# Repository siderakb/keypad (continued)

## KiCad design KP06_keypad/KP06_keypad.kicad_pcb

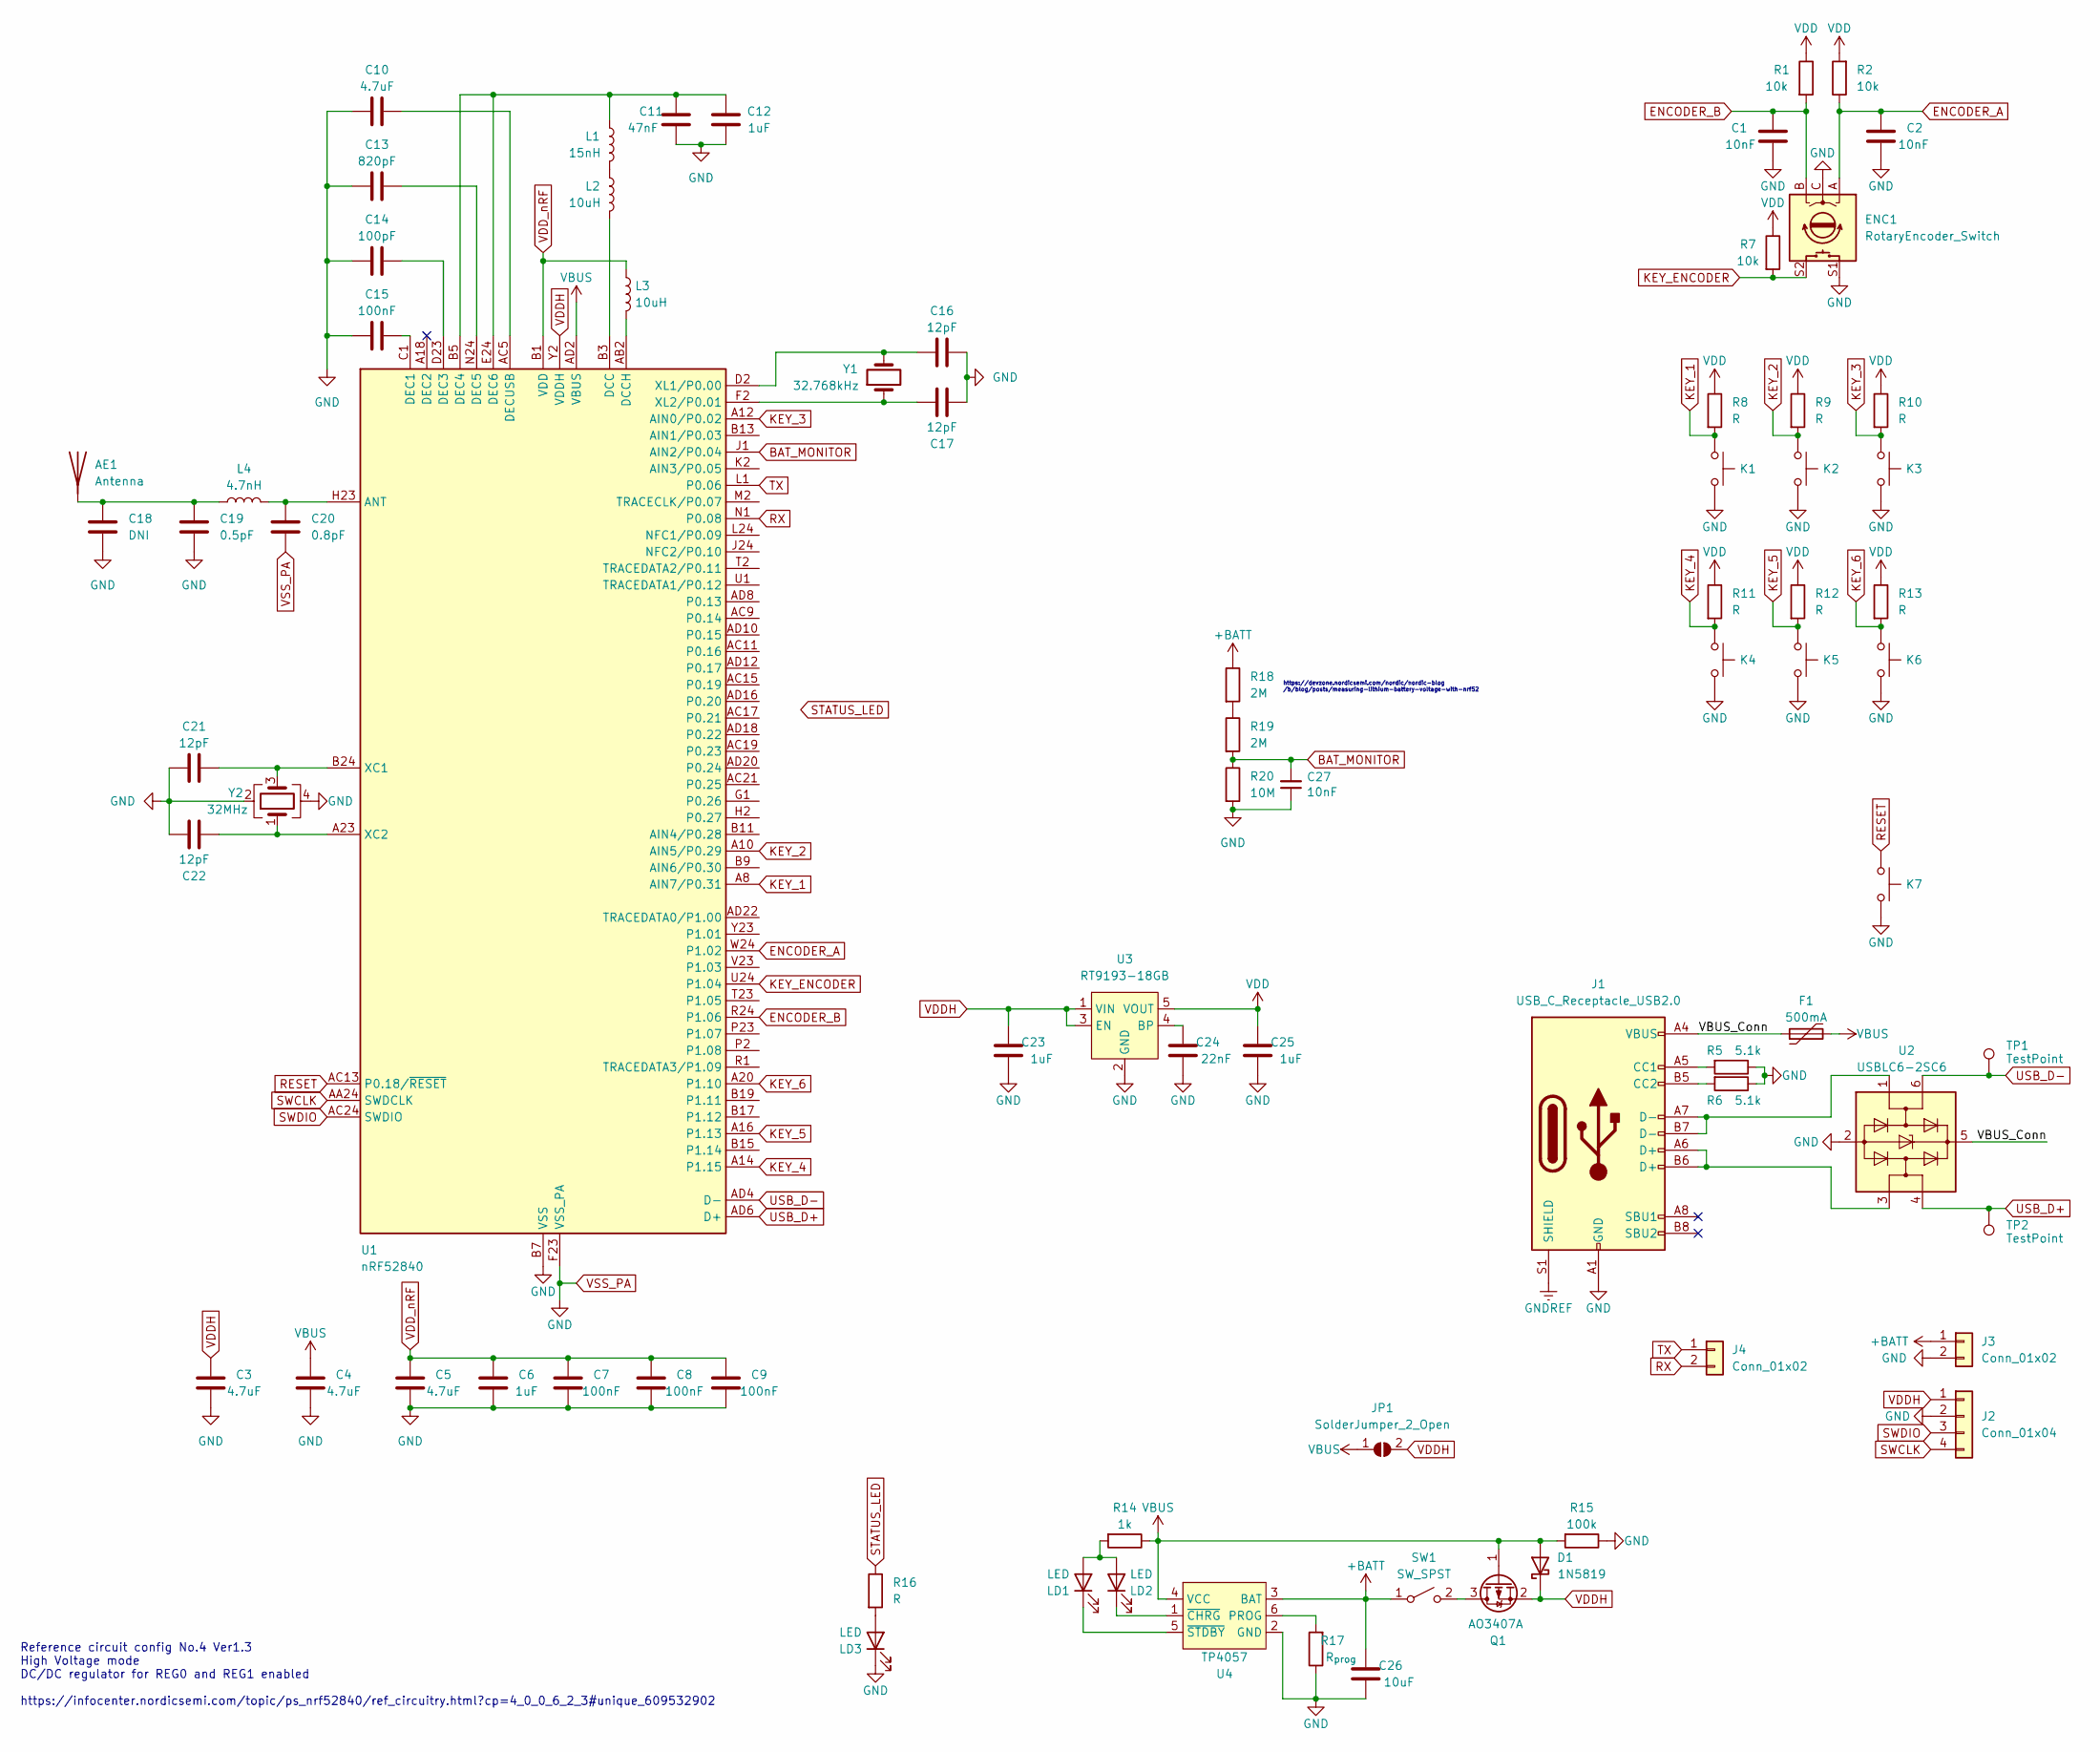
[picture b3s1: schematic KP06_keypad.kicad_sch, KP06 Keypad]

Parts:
AE1: Antenna; Texas_SWRA117D_2.4GHz_Left
C1, C2, C27: 10nF; C_0603_1608Metric
C3, C4, C5, C10: 4.7uF; C_0603_1608Metric
C6, C12, C23, C25: 1uF; C_0603_1608Metric
C7, C8, C9, C15: 100nF; C_0402_1005Metric
C11: 47nF; C_0402_1005Metric
C13: 820pF; C_0402_1005Metric
C14: 100pF; C_0402_1005Metric
C16, C17, C21, C22: 12pF; C_0402_1005Metric
C18: DNI; C_0402_1005Metric
C19: 0.5pF; C_0402_1005Metric
C20: 0.8pF; C_0402_1005Metric
C24: 22nF; C_0603_1608Metric
C26: 10uF; C_0603_1608Metric
D1: 1N5819; D_SOD-123
ENC1: RotaryEncoder_Switch; RotaryEncoder_Alps_EC11E-Switch_Vertical_H20mm
F1: 500mA; Fuse_1206_3216Metric
J1: USB_C_Receptacle_USB2.0; USB_C_Receptacle_HRO_TYPE-C-31-M-12
J2: Conn_01x04; PinHeader_1x04_P2.54mm_Vertical
J3: Conn_01x02; JST_PH_B2B-PH-K_1x02_P2.00mm_Vertical
J4: Conn_01x02; PinHeader_1x02_P2.00mm_Vertical
JP1: SolderJumper_2_Open; SolderJumper-2_P1.3mm_Open_TrianglePad1.0x1.5mm
K1, K2, K3, K4, K5, K6: SW_Push; MX_switch_Gateron_hotswap_A
K7: SW_Push; SW_SPST_PTS645
L1: 15nH; L_0402_1005Metric
L2, L3: 10uH; L_0603_1608Metric
L4: 4.7nH; L_0402_1005Metric
LD1, LD2, LD3: LED; LED_0603_1608Metric
Q1: AO3407A; SOT-23
R1, R2, R7: 10k; R_0603_1608Metric
R5, R6: 5.1k; R_0603_1608Metric
R8, R9, R10, R11, R12, R13, R16: R; R_0603_1608Metric
R14: 1k; R_0603_1608Metric
R15: 100k; R_0603_1608Metric
R17: R_{prog}; R_0603_1608Metric
R18, R19: 2M; R_0603_1608Metric
R20: 10M; R_0603_1608Metric
SW1: SW_SPST; SW_SPDT_PCM12
TP1, TP2: TestPoint; TestPoint_Pad_D2.0mm
U1: nRF52840; Nordic_AQFN-73-1EP_7x7mm_P0.5mm
U2: USBLC6-2SC6; SOT-23-6
U3: RT9193-18GB; SOT-23-5
U4: TP4057; SOT-23-6
Y1: 32.768kHz; Crystal_SMD_3215-2Pin_3.2x1.5mm
Y2: 32MHz; Crystal_SMD_2016-4Pin_2.0x1.6mm

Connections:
+BATT: C26.2, J3.1, R18.1, SW1.1 (A), U4.3 (BAT)
/VBUS_Conn: F1.1, J1.A4 (VBUS), J1.A9 (VBUS), J1.B4 (VBUS), J1.B9 (VBUS), U2.5 (VBUS)
BAT_MONITOR: C27.2, R19.2, R20.1, U1.J1 (AIN2/P0.04)
ENCODER_A: C2.1, ENC1.A, R2.1, U1.W24 (P1.02)
ENCODER_B: C1.2, ENC1.B, R1.2, U1.R24 (P1.06)
GNDREF: J1.S1 (SHIELD)
KEY_1: K1.1, R8.2, U1.A8 (AIN7/P0.31)
KEY_2: K2.1, R9.2, U1.A10 (AIN5/P0.29)
KEY_3: K3.1, R10.2, U1.A12 (AIN0/P0.02)
KEY_4: K4.1, R11.2, U1.A14 (P1.15)
KEY_5: K5.1, R12.2, U1.A16 (P1.13)
KEY_6: K6.1, R13.2, U1.A20 (P1.10)
KEY_ENCODER: ENC1.S2, R7.2, U1.U24 (P1.04)
unnamed: AE1.1 (A), C18.1, C19.1, L4.1
unnamed: C10.2, U1.AC5 (DECUSB)
unnamed: C11.2, C12.2, L1.1, U1.B5 (DEC4), U1.E24 (DEC6)
unnamed: C13.2, U1.N24 (DEC5)
unnamed: C14.2, U1.D23 (DEC3)
unnamed: C15.2, U1.C1 (DEC1)
unnamed: C16.1, U1.D2 (XL1/P0.00), Y1.2
unnamed: C17.1, U1.F2 (XL2/P0.01), Y1.1
unnamed: C20.1, L4.2, U1.H23 (ANT)
unnamed: C21.2, U1.B24 (XC1), Y2.3
unnamed: C22.2, U1.A23 (XC2), Y2.1
unnamed: C24.2, U3.4 (BP)
unnamed: J1.A5 (CC1), R5.2
unnamed: J1.A6 (D+), J1.B6 (D+), U2.3 (I/O2)
unnamed: J1.A7 (D-), J1.B7 (D-), U2.1 (I/O1)
unnamed: J1.B5 (CC2), R6.2
unnamed: L1.2, L2.1
unnamed: L2.2, U1.B3 (DCC)
unnamed: L3.2, U1.AB2 (DCCH)
unnamed: LD1.1 (K), U4.5 (~STDBY)
unnamed: LD1.2 (A), LD2.2 (A), R14.2
unnamed: LD2.1 (K), U4.1 (~CHRG)
unnamed: LD3.2 (A), R16.2
unnamed: Q1.3 (D), SW1.2 (B)
unnamed: R17.2, U4.6 (PROG)
unnamed: R18.2, R19.1
RESET: K7.1, U1.AC13 (P0.18/~RESET)
RX: J4.2, U1.N1 (P0.08)
STATUS_LED: R16.1
SWCLK: J2.4, U1.AA24 (SWDCLK)
SWDIO: J2.3, U1.AC24 (SWDIO)
TX: J4.1, U1.L1 (P0.06)
USB_D+: TP2.1, U1.AD6 (D+), U2.4 (I/O2)
USB_D-: TP1.1, U1.AD4 (D-), U2.6 (I/O1)
VBUS: C4.2, D1.2 (A), F1.2, JP1.1 (A), Q1.1 (G), R14.1, R15.2, U1.AD2 (VBUS), U4.4 (VCC)
VDD: C25.2, R1.1, R2.2, R7.1, R8.1, R9.1, R10.1, R11.1, R12.1, R13.1, U3.5 (VOUT)
VDDH: C3.2, C23.2, D1.1 (K), J2.1, JP1.2 (B), Q1.2 (S), U1.Y2 (VDDH), U3.1 (VIN), U3.3 (EN)
VDD_nRF: C5.2, C6.2, C7.2, C8.2, C9.2, L3.1, U1.A22 (VDD), U1.AD14 (VDD), U1.AD23 (VDD), U1.B1 (VDD), U1.W1 (VDD)
VSS_PA: C1.1, C2.2, C3.1, C4.1, C5.1, C6.1, C7.1, C8.1, C9.1, C10.1, C11.1, C12.1, C13.1, C14.1, C15.1, C16.2, C17.2, C18.2, C19.2, C20.2, C21.1, C22.1, C23.1, C24.1, C25.1, C26.1, C27.1, ENC1.C, ENC1.S1, J1.A1 (GND), J1.A12 (GND), J1.B1 (GND), J1.B12 (GND), J2.2, J3.2, K1.2, K2.2, K3.2, K4.2, K5.2, K6.2, K7.2, LD3.1 (K), R5.1, R6.1, R15.1, R17.1, R20.2, U1.B7 (VSS), U1.EP (VSS), U1.F23 (VSS_PA), U2.2 (GND), U3.2 (GND), U4.2 (GND), Y2.2, Y2.4

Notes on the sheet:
Reference circuit config No.4 Ver1.3 High Voltage mode DC/DC regulator for REG0 and REG1 enabled https://infocenter.nordicsemi.com/topic/ps_nrf52840/ref_circuitry.html?cp=4_0_0_6_2_3#unique_609532902
https://devzone.nordicsemi.com/nordic/nordic-blog /b/blog/posts/measuring-lithium-battery-voltage-with-nrf52

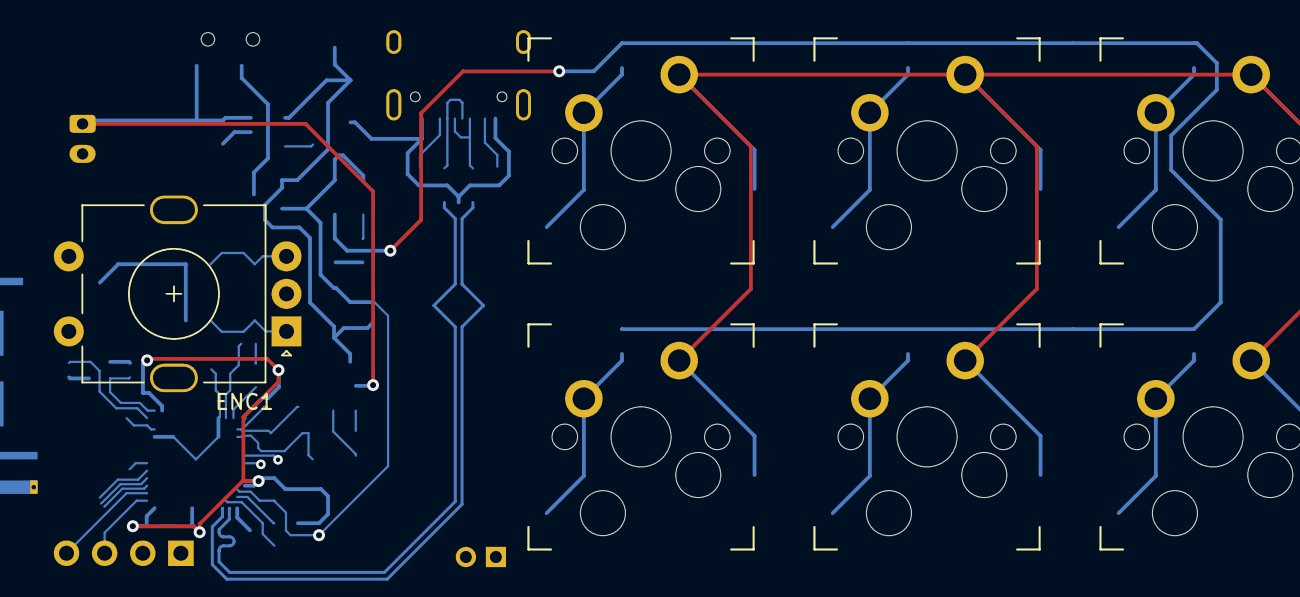
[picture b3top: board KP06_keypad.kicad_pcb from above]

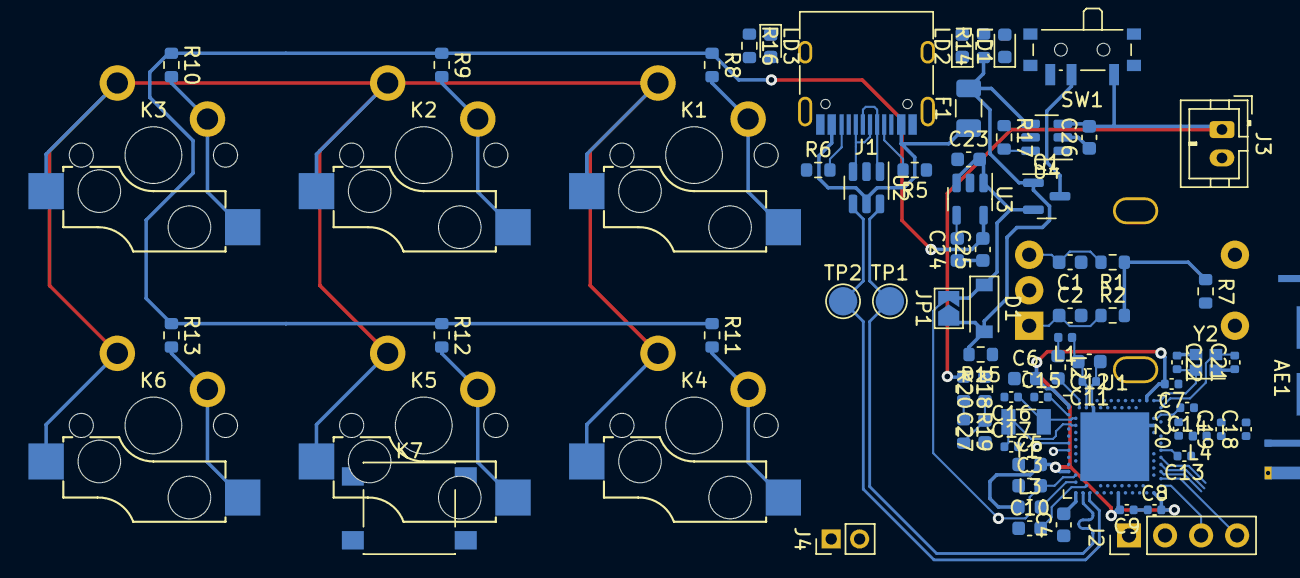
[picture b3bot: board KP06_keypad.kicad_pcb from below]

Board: 2 copper layers, 78 parts (71 on the bottom side), 50 nets.

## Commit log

2022-10-23 Add KiCad project
2022-10-23 Move files
2022-10-23 Create LICENSE
2022-10-26 Add keyswitch footprint library submodule
2022-11-01 Create KP08 KiCad project
2022-11-01 Update KP08
2022-11-02 Update footprint
2022-11-02 Change mount hole from M3 to M2
2022-11-04 Update submodule
2022-11-04 Add 'KP08Hub' KiCad project
2022-11-06 Update KP08Hub
2022-11-12 Add gerber files
2022-11-12 Add schematic
